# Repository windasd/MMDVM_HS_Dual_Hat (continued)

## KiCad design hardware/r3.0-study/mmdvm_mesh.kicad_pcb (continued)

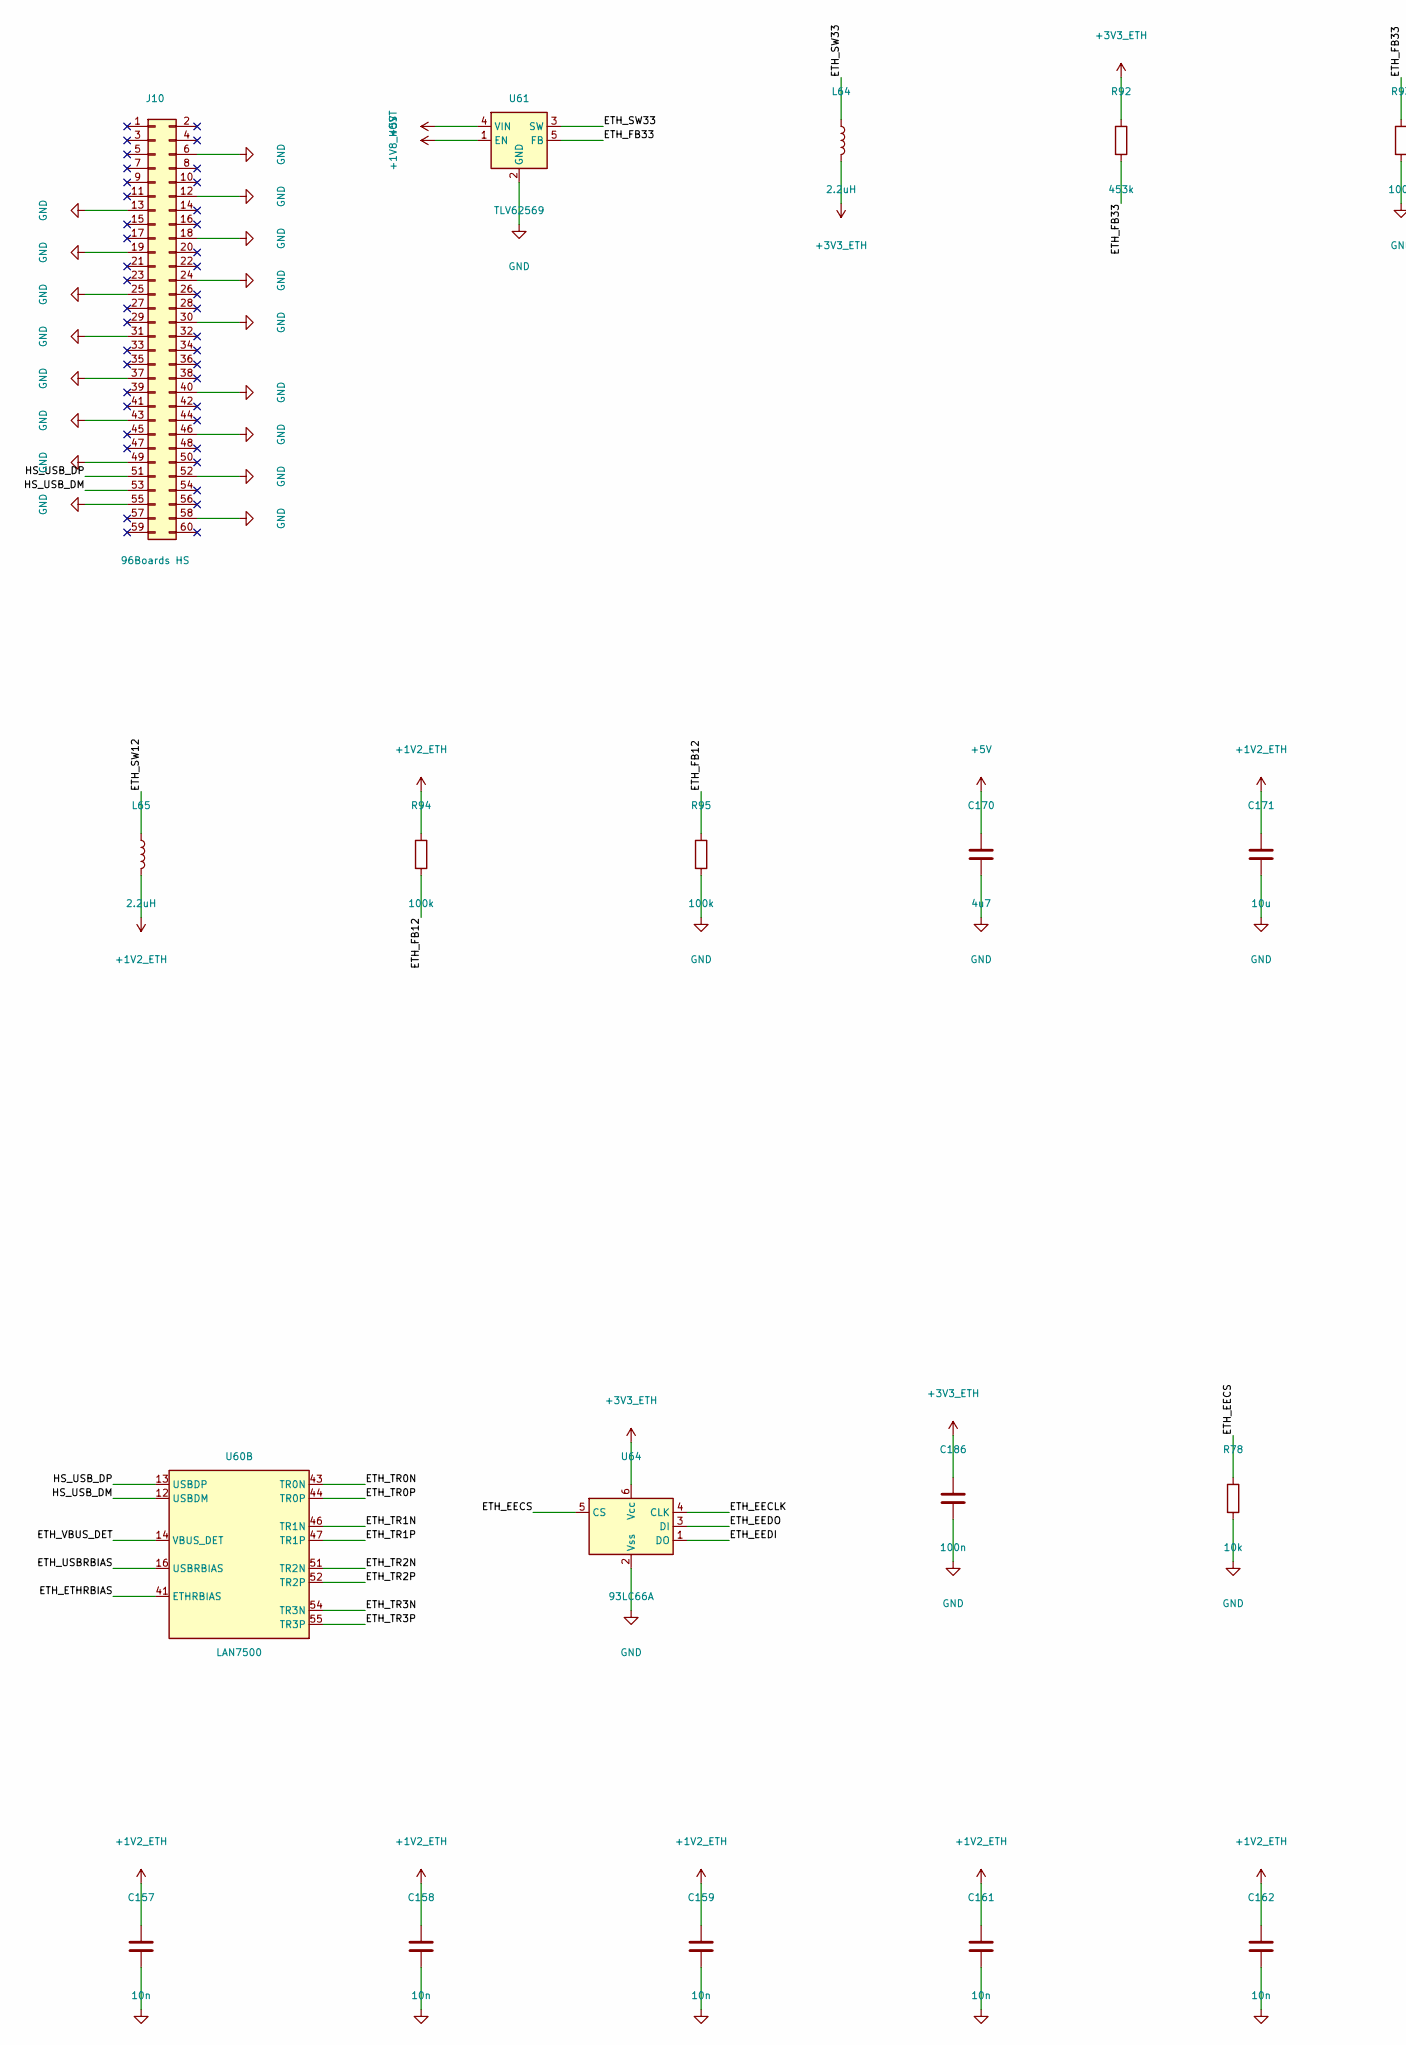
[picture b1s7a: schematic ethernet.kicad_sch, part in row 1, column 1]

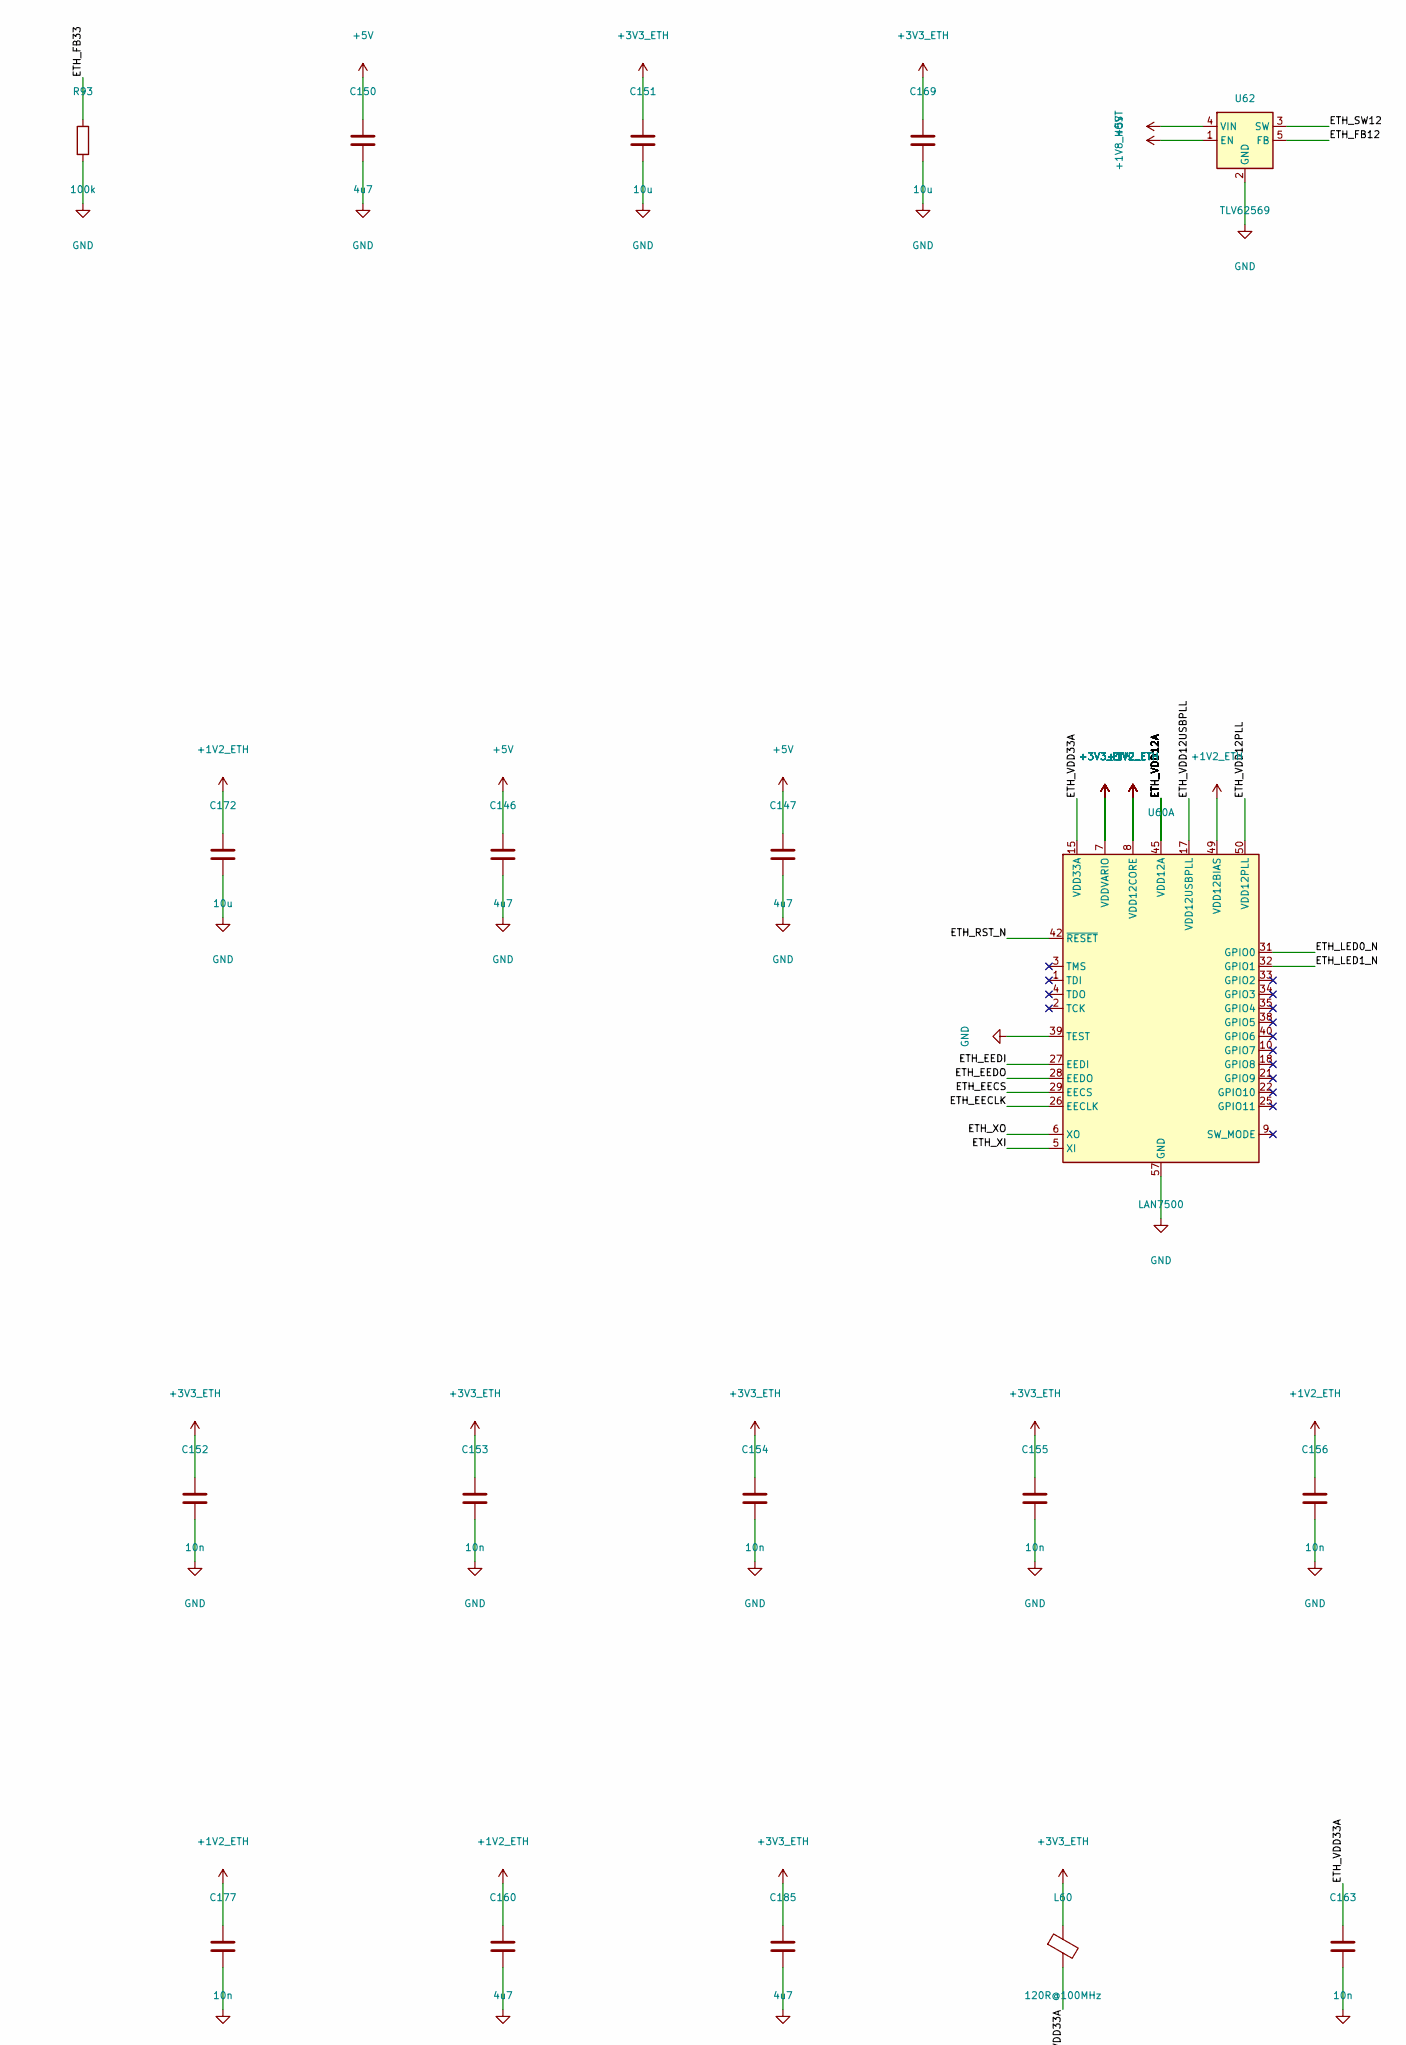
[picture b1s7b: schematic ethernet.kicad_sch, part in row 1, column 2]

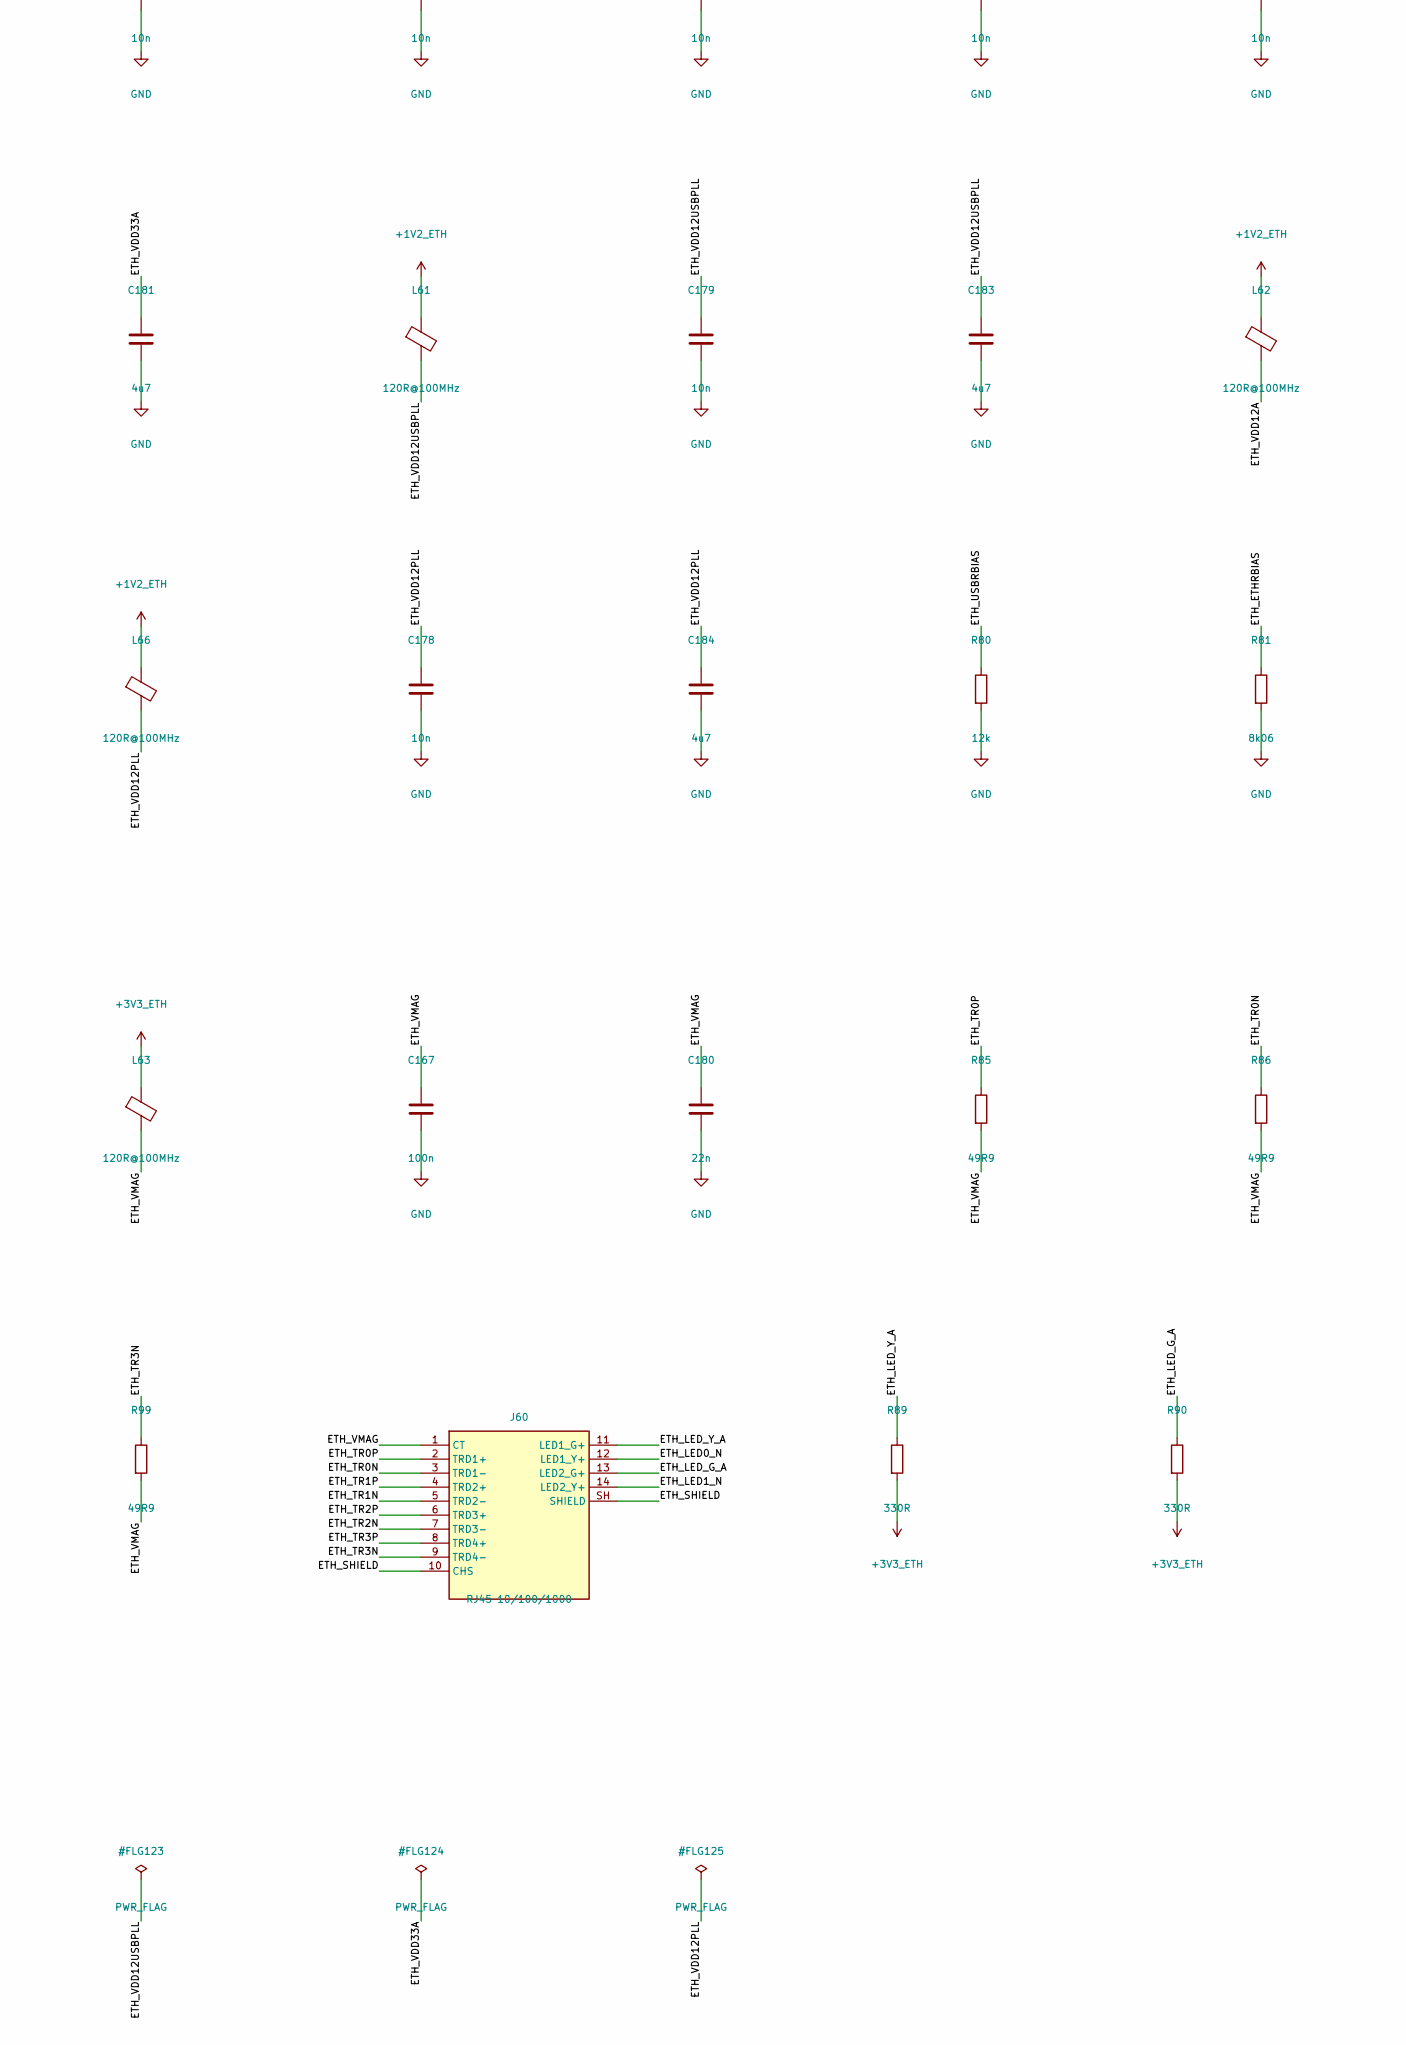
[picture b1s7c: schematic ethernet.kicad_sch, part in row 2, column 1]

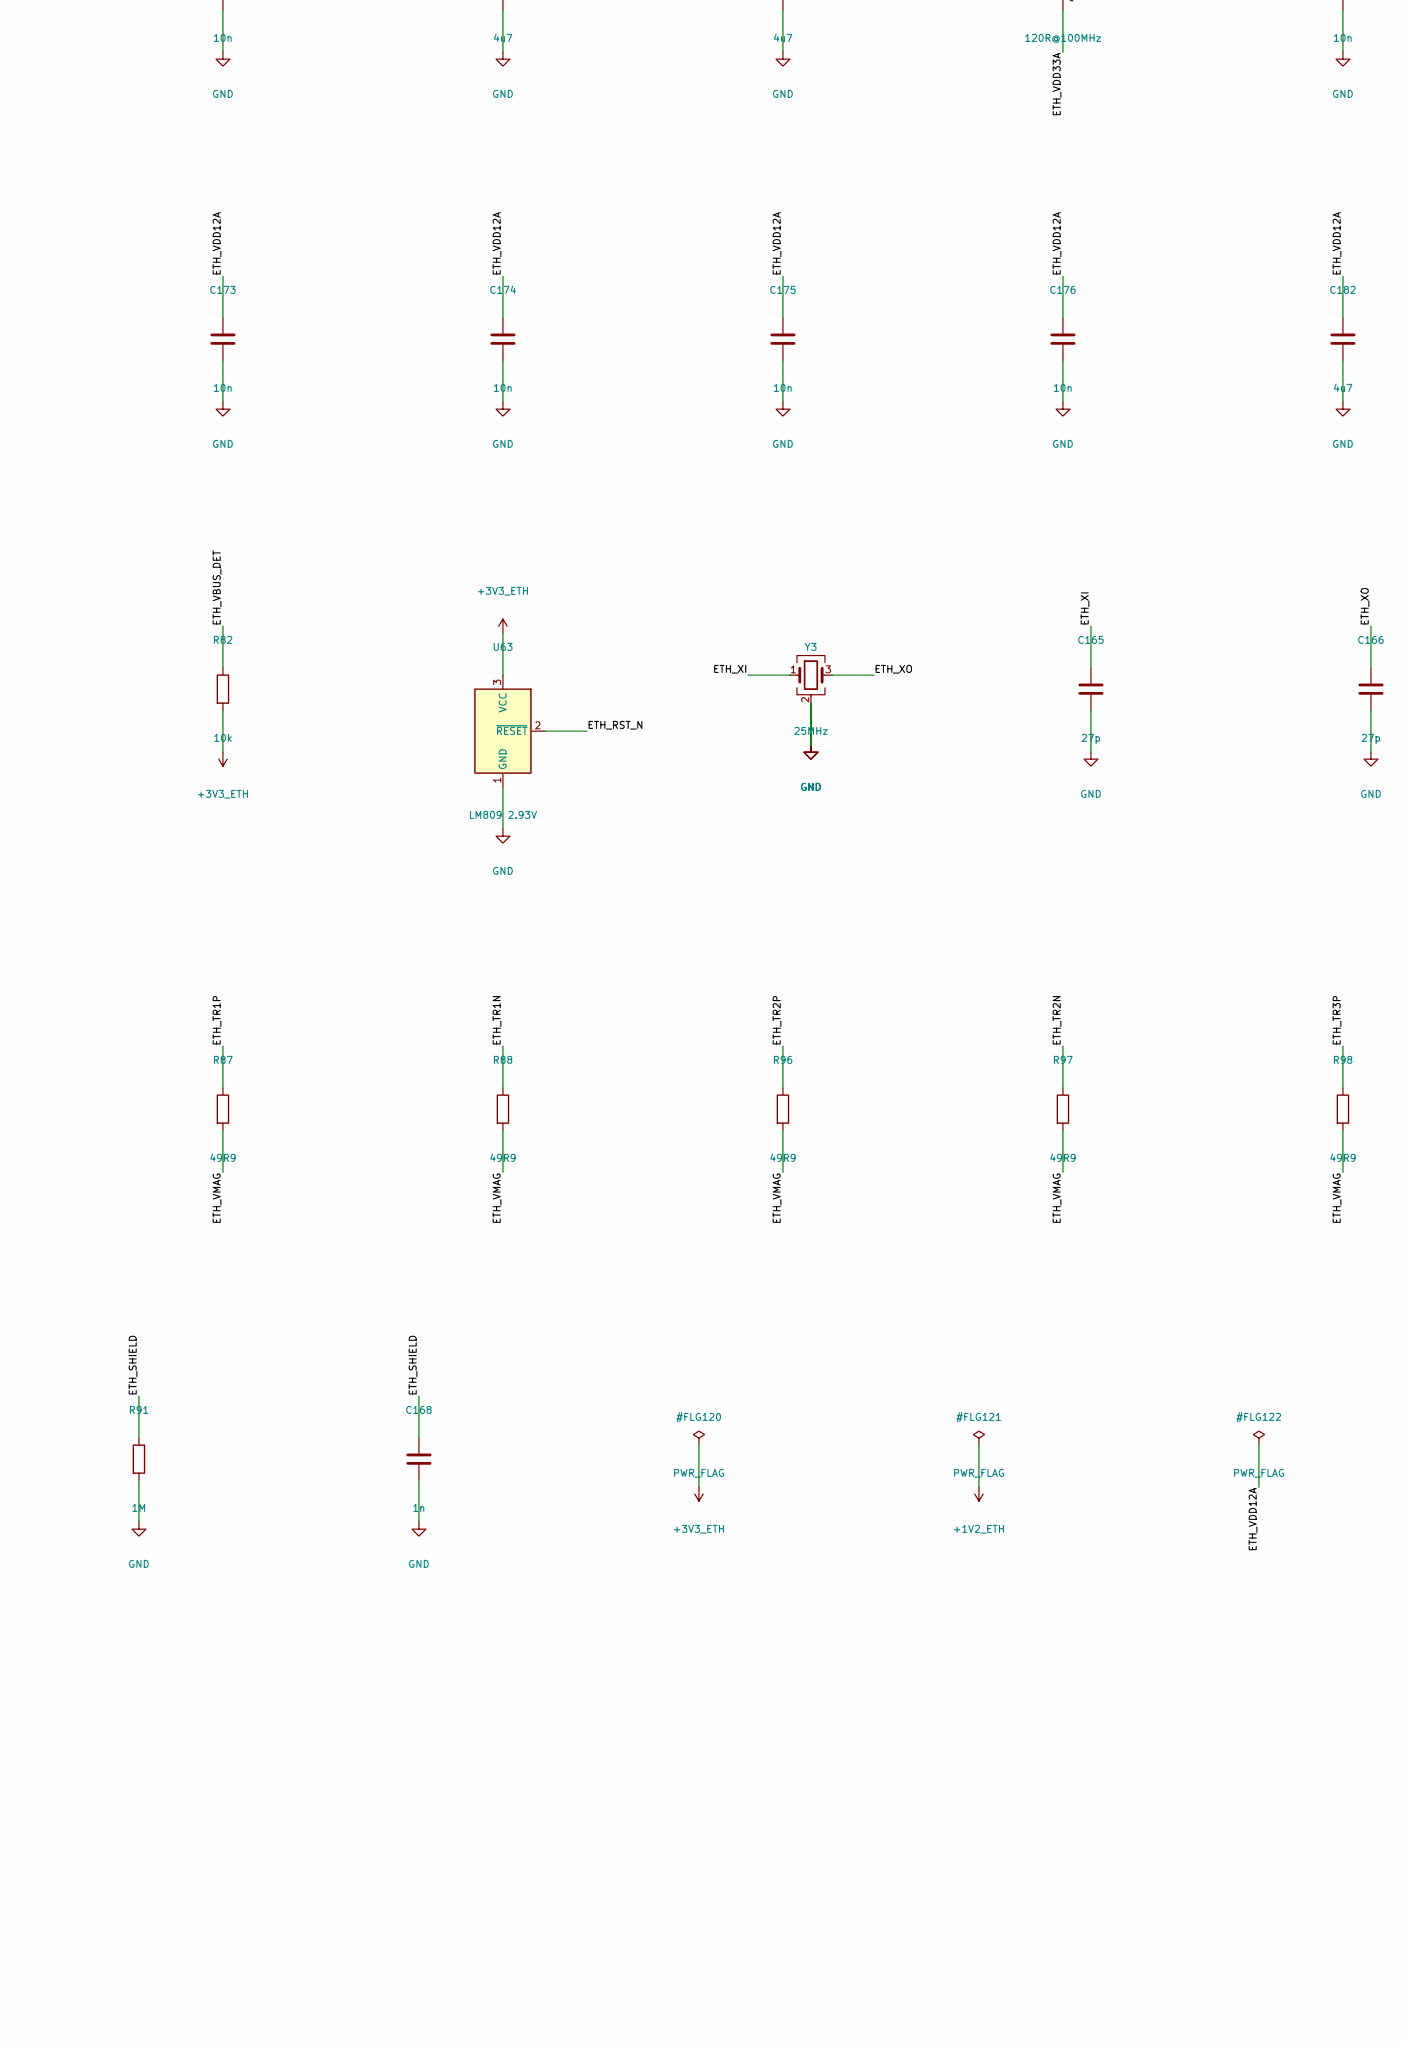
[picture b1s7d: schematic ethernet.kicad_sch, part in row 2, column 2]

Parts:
C146, C147: 4u7; C_0402_1005Metric; MPN CL05A475MP5NRNC; LCSC C23733
C150, C160, C170, C181, C182, C183, C184, C185: 4u7; C_0603_1608Metric; MPN CL10A475KO8NNNC; Mouser 187-CL10A475KO8NNNC
C151, C169, C171, C172: 10u; C_0603_1608Metric; MPN CL10A106MA8NRNC; Mouser 187-CL10A106MA8NRNC
C152, C153, C154, C155, C156, C157, C158, C159, C161, C162, C163, C173, C174, C175, C176, C177, C178, C179: 10n; C_0402_1005Metric; MPN CL05B103KB5NNNC; Mouser 187-CL05B103KB5NNNC
C165, C166: 27p; C_0402_1005Metric; MPN CL05C270JB5NNNC; LCSC C86287
C167, C186: 100n; C_0402_1005Metric; MPN CL05B104KO5NNNC; Mouser 187-CL05B104KO5NNNC
C168: 1n; C_1206_3216Metric; MPN CC1206KKX7RDBB102; LCSC C23631
C180: 22n; C_0402_1005Metric; MPN 0402B223K500NT; Mouser 187-CL05B223KB5NNNC (Mouser EQUIV: CL05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
J10: 96Boards HS; AMPHENOL_61083-063402LF; MPN 61083-063402LF; Mouser 649-61083-063402LF
J60: RJ45 10/100/1000; RJ45_Wuerth_7499111446_EdgeMount; MPN 7499111446; Mouser 710-7499111446
L60, L61, L62, L63, L66: 120R@100MHz; L_0603_1608Metric; MPN BLM18PG121SN1D; Mouser 81-BLM18PG121SN1D
L64, L65: 2.2uH; L_1008_2520Metric; MPN DFE252012F-2R2M=P2; Mouser 81-DFE252012F-2R2MP2
R78, R82: 10k; R_0402_1005Metric; MPN 0402WGF1002TCE; Mouser 603-RC0402FR-0710KL
R80: 12k; R_0402_1005Metric; MPN 0402WGF1202TCE; LCSC C25752
R81: 8k06; R_0402_1005Metric; MPN 0402WGF8061TCE; LCSC C25923
R85, R86, R87, R88, R96, R97, R98, R99: 49R9; R_0402_1005Metric; MPN 0402WGF499JTCE; LCSC C25120
R89, R90: 330R; R_0402_1005Metric; MPN 0402WGF3300TCE; Mouser 603-RC0402FR-07330RL
R91: 1M; R_1210_3225Metric; MPN 1210W2F1004T5E; Mouser 603-RC1210FR-071ML
R92: 453k; R_0402_1005Metric; MPN 0402WGF4533TCE; Mouser 603-RC0402FR-07453KL
R93, R94, R95: 100k; R_0402_1005Metric; MPN 0402WGF1003TCE; Mouser 603-RC0402FR-07100KL
U60: LAN7500; QFN-56-1EP_8x8mm_P0.5mm_EP5.9x5.9mm; MPN LAN7500I-ABZJ; Mouser 579-LAN7500-ABZJ
U61, U62: TLV62569; SOT-23-5; MPN TLV62569DBVR; Mouser 595-TLV62569DBVR
U63: LM809 2.93V; SOT-23; MPN LM809M3X-2.93/NOPB; Mouser 926-LM809M3X293NOPB
U64: 93LC66A; SOT-23-6; MPN 93LC66AT-I/OT; Mouser 579-93AA66AT-I/OT
Y3: 25MHz; Crystal_SMD_3225-4Pin_3.2x2.5mm; MPN X322525MRB4SI; Mouser 717-7M-25.000MAAJ-T

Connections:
+1V2_ETH: C156.1, C157.1, C158.1, C159.1, C160.1, C161.1, C162.1, C171.1, C172.1, C177.1, L61.1, L62.1, L65.2, L66.1, R94.1, U60.8 (VDD12CORE), U60.11 (VDD12CORE), U60.20 (VDD12CORE), U60.23 (VDD12CORE), U60.30 (VDD12CORE), U60.36 (VDD12CORE), U60.49 (VDD12BIAS)
+1V8_HOST: U61.1 (EN), U62.1 (EN); also elsewhere on the board
+3V3_ETH: C151.1, C152.1, C153.1, C154.1, C155.1, C169.1, C185.1, C186.1, L60.1, L63.1, L64.2, R82.2, R89.2, R90.2, R92.1, U60.7 (VDDVARIO), U60.19 (VDDVARIO), U60.24 (VDDVARIO), U60.37 (VDDVARIO), U63.3 (VCC), U64.6 (Vcc)
+5V: C146.1, C147.1, C150.1, C170.1, U61.4 (VIN), U62.4 (VIN); also elsewhere on the board
/Ethernet/ETH_EECLK: U60.26 (EECLK), U64.4 (CLK)
/Ethernet/ETH_EECS: R78.1, U60.29 (EECS), U64.5 (CS)
/Ethernet/ETH_EEDI: U60.27 (EEDI), U64.1 (DO)
/Ethernet/ETH_EEDO: U60.28 (EEDO), U64.3 (DI)
/Ethernet/ETH_ETHRBIAS: R81.1, U60.41 (ETHRBIAS)
/Ethernet/ETH_FB12: R94.2, R95.1, U62.5 (FB)
/Ethernet/ETH_FB33: R92.2, R93.1, U61.5 (FB)
/Ethernet/ETH_LED0_N: J60.12 (LED1_Y+), U60.31 (GPIO0)
/Ethernet/ETH_LED1_N: J60.14 (LED2_Y+), U60.32 (GPIO1)
/Ethernet/ETH_LED_G_A: J60.13 (LED2_G+), R90.1
/Ethernet/ETH_LED_Y_A: J60.11 (LED1_G+), R89.1
/Ethernet/ETH_RST_N: U60.42 (~RESET), U63.2 (~RESET)
/Ethernet/ETH_SHIELD: C168.1, J60.10 (CHS), J60.SH (SHIELD), R91.1
/Ethernet/ETH_SW12: L65.1, U62.3 (SW)
/Ethernet/ETH_SW33: L64.1, U61.3 (SW)
/Ethernet/ETH_TR0N: J60.3 (TRD1-), R86.1, U60.43 (TR0N)
/Ethernet/ETH_TR0P: J60.2 (TRD1+), R85.1, U60.44 (TR0P)
/Ethernet/ETH_TR1N: J60.5 (TRD2-), R88.1, U60.46 (TR1N)
/Ethernet/ETH_TR1P: J60.4 (TRD2+), R87.1, U60.47 (TR1P)
/Ethernet/ETH_TR2N: J60.7 (TRD3-), R97.1, U60.51 (TR2N)
/Ethernet/ETH_TR2P: J60.6 (TRD3+), R96.1, U60.52 (TR2P)
/Ethernet/ETH_TR3N: J60.9 (TRD4-), R99.1, U60.54 (TR3N)
/Ethernet/ETH_TR3P: J60.8 (TRD4+), R98.1, U60.55 (TR3P)
/Ethernet/ETH_USBRBIAS: R80.1, U60.16 (USBRBIAS)
/Ethernet/ETH_VBUS_DET: R82.1, U60.14 (VBUS_DET)
/Ethernet/ETH_VDD12A: C173.1, C174.1, C175.1, C176.1, C182.1, L62.2, U60.45 (VDD12A), U60.48 (VDD12A), U60.53 (VDD12A), U60.56 (VDD12A)
/Ethernet/ETH_VDD12PLL: C178.1, C184.1, L66.2, U60.50 (VDD12PLL)
/Ethernet/ETH_VDD12USBPLL: C179.1, C183.1, L61.2, U60.17 (VDD12USBPLL)
/Ethernet/ETH_VDD33A: C163.1, C181.1, L60.2, U60.15 (VDD33A)
/Ethernet/ETH_VMAG: C167.1, C180.1, J60.1 (CT), L63.2, R85.2, R86.2, R87.2, R88.2, R96.2, R97.2, R98.2, R99.2
/Ethernet/ETH_XI: C165.1, U60.5 (XI), Y3.1
/Ethernet/ETH_XO: C166.1, U60.6 (XO), Y3.3
/Ethernet/HS_USB_DM: J10.53, U60.12 (USBDM)
/Ethernet/HS_USB_DP: J10.51, U60.13 (USBDP)
GND: C146.2, C147.2, C150.2, C151.2, C152.2, C153.2, C154.2, C155.2, C156.2, C157.2, C158.2, C159.2, C160.2, C161.2, C162.2, C163.2, C165.2, C166.2, C167.2, C168.2, C169.2, C170.2, C171.2, C172.2, C173.2, C174.2, C175.2, C176.2, C177.2, C178.2, C179.2, C180.2, C181.2, C182.2, C183.2, C184.2, C185.2, C186.2, J10.6, J10.12, J10.13, J10.18, J10.19, J10.24, J10.25, J10.30, J10.31, J10.37, J10.40, J10.43, J10.46, J10.49, J10.52, J10.55, J10.58, R78.2, R80.2, R81.2, R91.2, R93.2, R95.2, U60.39 (TEST), U60.57 (GND), U61.2 (GND), U62.2 (GND), U63.1 (GND), U64.2 (Vss), Y3.2 (G), Y3.4 (G); also elsewhere on the board

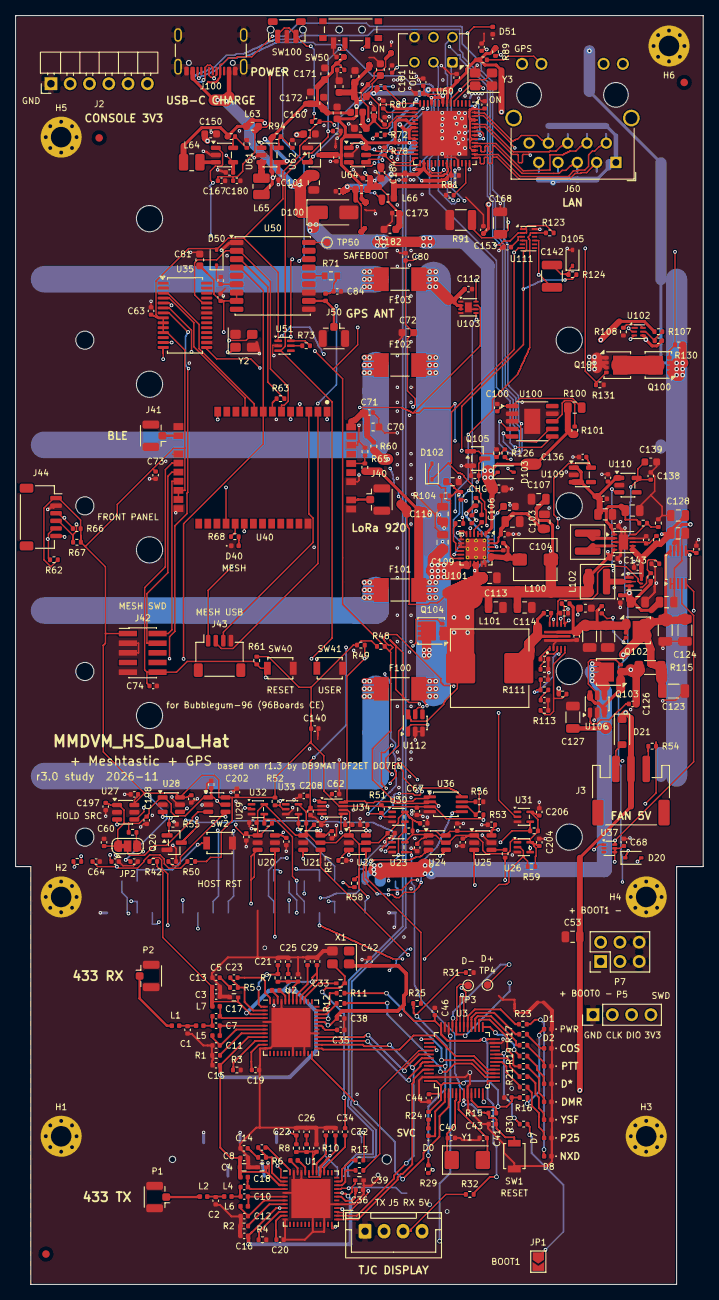
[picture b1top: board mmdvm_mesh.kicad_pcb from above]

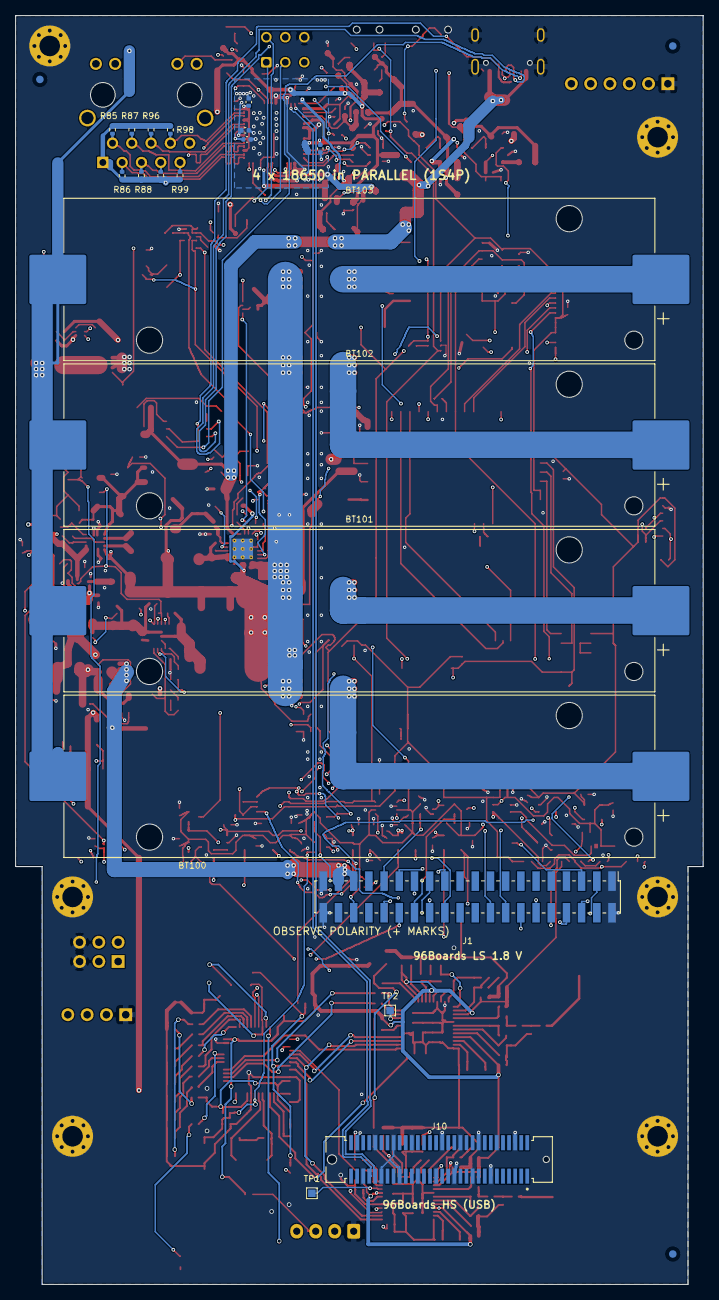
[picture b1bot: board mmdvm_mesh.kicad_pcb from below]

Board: 4 copper layers, 90.5 x 167.0 mm, 432 parts (23 on the bottom side), 263 nets.

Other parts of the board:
C187, C188, C189, C190, C191, C192, C193, C194, C195, C196, C197, C198, C199, C200, C201, C202, C203, C204, C205, C206, C207, C208: 100n; C_0402_1005Metric
FID1, FID2, FID3, FID4, FID5, FID6: Fiducial_1mm_Mask2mm
H1, H2, H3, H4, H5, H6: MountingHole_2.7mm_M2.5_Pad_Via

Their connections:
+1V8_HOST: C187.1, C189.1, C191.1, C193.1, C195.1, C197.1, C199.1, C201.1, C203.1, C204.1, C205.1, C206.1, C207.1, C208.1; also elsewhere on the board
+3V3: C188.1, C190.1, C192.1, C194.1, C196.1; also elsewhere on the board
+3V3_MESH: C198.1, C200.1, C202.1; also elsewhere on the board
GND: C187.2, C188.2, C189.2, C190.2, C191.2, C192.2, C193.2, C194.2, C195.2, C196.2, C197.2, C198.2, C199.2, C200.2, C201.2, C202.2, C203.2, C204.2, C205.2, C206.2, C207.2, C208.2, H1.1, H2.1, H3.1, H4.1, H5.1, H6.1; also elsewhere on the board

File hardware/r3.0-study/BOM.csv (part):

"Reference","Value","Footprint","Qty","MFR","MPN","Mouser","Mouser MPN (if different)","LCSC"
"BT100,BT101,BT102,BT103","18650","Battery:BatteryHolder_Keystone_1042_1x18650","4","Keystone Electronics","1042P","534-1042P","","C6038009"
"C1,C2,C11,C12","6p8","Capacitor_SMD:C_0402_1005Metric","4","Murata Electronics","GJM1555C1H6R8BB01D","81-GJM1555C1H6R8BB1D","","C88896"
"C3,C15,C16,C31,C32,C38,C42","10n","Capacitor_SMD:C_0402_1005Metric","7","Vishay / Vitramon","VJ0402Y103KXJCW1BC","77-VJ0402Y103KXJCBC","","C15195"
"C4,C17,C18,C39","10n","MMDVM:C_0402","4","Vishay / Vitramon","VJ0402Y103KXJCW1BC","77-VJ0402Y103KXJCBC","","C15195"
"C5,C8","220p","Capacitor_SMD:C_0402_1005Metric","2","Murata Electronics","GRM1555C1H221JA01D","81-GRM1555C1H221JA01","","C71693"
"C6,C9","10p","Capacitor_SMD:C_0402_1005Metric","2","Murata Electronics","GRM1555C1E100GA01D","81-GRM1555C1E100GA1D","","C76945"
"C7,C10","4p7","Capacitor_SMD:C_0402_1005Metric","2","Murata Electronics","GRM1555C1H4R7CA01D","81-GRM1555C1H4R7CA1D","","C85883"
"C13,C14,C19,C20,C29,C30,C35,C36","100n","Capacitor_SMD:C_0402_1005Metric","8","Murata Electronics","GCM155R71C104KA55D","81-GCM155R71C104KA5J","GCM155R71C104KA55J","C1525"
"C21,C22","470p","Capacitor_SMD:C_0402_1005Metric","2","Murata Electronics","GCM1555C1H471JA16J","81-GCM1555C1H471JA6J","","C76971"
"C23,C24","22n","Capacitor_SMD:C_0402_1005Metric","2","Murata Electronics","GCM155R71E223KA55D","81-GCM155R71E223KA5D","","C126528"
"C25,C26","15n","Capacitor_SMD:C_0402_1005Metric","2","Murata Electronics","GRM155R71C153KA01J","81-GRM155R71C153KA1J","","C113050"
"C27,C28","1n","Capacitor_SMD:C_0402_1005Metric","2","Murata Electronics","GRM155R60J102KA01D","81-GRM155R60J102KA1D","","C710871"
"C33","22p","MMDVM:C_0402","1","Kyocera AVX","KGM05ACG1H220GH","581-KGM05ACG1H220GH","","C161541"
"C34","22p","Capacitor_SMD:C_0402_1005Metric","1","Kyocera AVX","KGM05ACG1H220GH","581-KGM05ACG1H220GH","","C161541"
"C40,C41","20p","Capacitor_SMD:C_0402_1005Metric","2","Murata Electronics","GJM1555C1H200FB01D","81-GJM1555C1H200FB1D","","C913479"
"C43,C44,C45,C46,C61,C62,C63,C64,C67,C68,C71,C73,C74,C82,C111,C112,C115,C125,C126,C131,C140,C167,C186","100n","Capacitor_SMD:C_0402_1005Metric","23","Samsung Electro-Mechanics","CL05B104KO5NNNC","187-CL05B104KO5NNNC","","C1525"
"C53,C101,C103,C104,C109,C110,C128,C132,C133,C134","10u","Capacitor_SMD:C_0805_2012Metric","10","Samsung Electro-Mechanics","CL21A106KAYNNNE","187-CL21A106KAYNNNE","","C15850"
"C60,C80,C83,C100,C135,C136,C137,C138,C141,C145,C148","1u","Capacitor_SMD:C_0402_1005Metric","11","Samsung Electro-Mechanics","CL05A105KA5NQNC","187-CL05A105KA5NQNC","","C52923"
"C65,C66","22p","Capacitor_SMD:C_0402_1005Metric","2","FH (Guangdong Fenghua Advanced Tech)","0402CG220J500NT","187-CL05C220JB5NNNC (Mouser EQUIV: CL05C220JB5NNNC)","","C1555"
"C70,C72,C81,C139,C151,C169,C171,C172","10u","Capacitor_SMD:C_0603_1608Metric","8","Samsung Electro-Mechanics","CL10A106MA8NRNC","187-CL10A106MA8NRNC","","C96446"
"C84,C152,C153,C154,C155,C156,C157,C158,C159,C161,C162,C163,C173,C174,C175,C176,C177,C178,C179","10n","Capacitor_SMD:C_0402_1005Metric","19","Samsung Electro-Mechanics","CL05B103KB5NNNC","187-CL05B103KB5NNNC","","C15195"
"C102","1u","Capacitor_SMD:C_0603_1608Metric","1","Samsung Electro-Mechanics","CL10A105KB8NNNC","187-CL10A105KB8NNNC","","C15849"
"C105","47n","Capacitor_SMD:C_0402_1005Metric","1","Samsung Electro-Mechanics","CL05B473KO5NNNC","187-CL05B473KO5NNNC","","C307434"
"C106,C116,C150,C160,C170,C181,C182,C183,C184,C185","4u7","Capacitor_SMD:C_0603_1608Metric","10","Samsung Electro-Mechanics","CL10A475KO8NNNC","187-CL10A475KO8NNNC","","C19666"
"C107,C108,C113,C114,C129,C130","22u","Capacitor_SMD:C_0805_2012Metric","6","Samsung Electro-Mechanics","CL21A226MAQNNNE","187-CL21A226MOQNNNE (Mouser EQUIV: CL21A226MOQNNNE)","","C45783"
"C117","6n8","Capacitor_SMD:C_0402_1005Metric","1","Samsung Electro-Mechanics","CL05B682KB5NNNC","187-CL05B682KB5NNNC","","C318580"
"C118","10p","Capacitor_SMD:C_0402_1005Metric","1","Samsung Electro-Mechanics","CL05C100JB5NNNC","187-CL05C100JB5NNNC","","C32949"
"C119,C120,C127","10u","Capacitor_SMD:C_1206_3216Metric","3","Samsung Electro-Mechanics","CL31A106KBHNNNE","187-CL31A106KBHNNNE","","C13585"
"C121,C180","22n","Capacitor_SMD:C_0402_1005Metric","2","FH (Guangdong Fenghua Advanced Tech)","0402B223K500NT","187-CL05B223KB5NNNC (Mouser EQUIV: CL05B223KB5NNNC)","","C1532"
"C122,C123,C124","22u","Capacitor_SMD:C_1206_3216Metric","3","Samsung Electro-Mechanics","CL31A226KAHNNNE","187-CL31A226KAHNNNE","","C12891"
"C143,C144","10u","Capacitor_SMD:C_0402_1005Metric","2","Samsung Electro-Mechanics","CL05A106MQ5NUNC","","","C15525"
"C146,C147,C149","4u7","Capacitor_SMD:C_0402_1005Metric","3","Samsung Electro-Mechanics","CL05A475MP5NRNC","","","C23733"
"C165,C166","27p","Capacitor_SMD:C_0402_1005Metric","2","Samsung Electro-Mechanics","CL05C270JB5NNNC","","","C86287"
"C168","1n","Capacitor_SMD:C_1206_3216Metric","1","Yageo","CC1206KKX7RDBB102","","","C23631"
"D0,D3,D7","red","LED_SMD:LED_0402_1005Metric","3","Kingbright","APHHS1005SURCK","604-APHHS1005SURCK","","C2852592"
"D1,D4,D40,D51","green","LED_SMD:LED_0402_1005Metric","4","Kingbright","APHHS1005LCGCK","604-APHHS1005CGCK","APHHS1005CGCK","C5354975"
"D2,D5","yellow","LED_SMD:LED_0402_1005Metric","2","Kingbright","APHHS1005SYCK","604-APHHS1005SYCK","","C5875733"
"D6","amber","LED_SMD:LED_0402_1005Metric","1","Kingbright","APHHS1005SECK","604-APHHS1005SECK","","C5875753"
"D8","blue","LED_SMD:LED_0402_1005Metric","1","Kingbright","APHHS1005QBC/D","604-APHHS1005QBCD","","C2853064"
"D21","B5819W","Diode_SMD:D_SOD-123","1","MCC (Micro Commercial Components)","B5819W-TP","833-B5819W-TP","","C84354"
"D50,D102","BAT54","Diode_SMD:D_SOD-323","2","onsemi","BAT54HT1G","863-BAT54HT1G","","C21107"
"D100","SMAJ15CA","Diode_SMD:D_SMA","1","Littelfuse","SMAJ15CA","576-SMAJ15CA","","C223985"
"D101","orange","LED_SMD:LED_0402_1005Metric","1","Kingbright","APHHS1005SECK","604-APHHS1005SECK","","C5875753"
"D103","6V2","Diode_SMD:D_SOD-323","1","onsemi","MM3Z6V2T1G","","","C393369"
"F100,F101,F102,F103","7A","Fuse:Fuse_Littelfuse-NANO2-451_453","4","Littelfuse","0451007.MRL","576-0451007.MRL","","C99548"
"J1","96Boards LS","MMDVM_r30:LS_2x20_P2.00mm_SMD_MezzanineBottom","1","Amphenol FCI","57202-G52-20LF","649-57202-G52-20LF","","C5422271"
"J2","CONSOLE 3V3","MMDVM_r30:PinHeader_1x06_P2.54mm_Horizontal_EdgeMount","1","Wurth Elektronik","61300611021","710-61300611021","","C6461553"
"J3","FAN 30x30x10 5V","Connector_JST:JST_PH_S3B-PH-SM4-TB_1x03-1MP_P2.00mm_Horizontal","1","JST","S3B-PH-SM4-TB(LF)(SN)","306-S3BPHSM4TBLFSN","","C265101"
"J5","TJC display","Connector_JST:JST_XH_B4B-XH-A_1x04_P2.50mm_Vertical","1","JST","B4B-XH-A(LF)(SN)","306-B4BXHALFSN","","C144395"
"J10","96Boards HS","MMDVM_r30:AMPHENOL_61083-063402LF","1","Amphenol ICC (FCI)","61083-063402LF","649-61083-063402LF","","C254700"
"J40","LoRa 920 U.FL","Connector_Coaxial:U.FL_Hirose_U.FL-R-SMT-1_Vertical","1","Hirose","U.FL-R-SMT-1(10)","798-U.FL-R-SMT-110","","C88373"
"J41","BLE U.FL","Connector_Coaxial:U.FL_Hirose_U.FL-R-SMT-1_Vertical","1","Hirose","U.FL-R-SMT-1(10)","798-U.FL-R-SMT-110","","C88373"
"J42","MESH SWD","Connector_PinHeader_1.27mm:PinHeader_2x05_P1.27mm_Vertical_SMD","1","Samtec","FTSH-105-01-F-DV-K","200-FTSH10501FDVK","","C5382952"
"J43","MESH USB","Connector_JST:JST_SH_SM04B-SRSS-TB_1x04-1MP_P1.00mm_Horizontal","1","JST","SM04B-SRSS-TB(LF)(SN)","306-SM04BSRSSTBLFSN","","C160404"
"J44","FRONT PANEL","Connector_JST:JST_SH_SM06B-SRSS-TB_1x06-1MP_P1.00mm_Horizontal","1","JST","SM06B-SRSS-TB(LF)(SN)","306-M06BSRSSTBLFSNPP","","C160405"
"J50","GPS U.FL","Connector_Coaxial:U.FL_Hirose_U.FL-R-SMT-1_Vertical","1","Hirose","U.FL-R-SMT-1(10)","798-U.FL-R-SMT-110","","C88373"
"J60","RJ45 10/100/1000","MMDVM_r30:RJ45_Wuerth_7499111446_EdgeMount","1","Wurth Elektronik","7499111446","710-7499111446","","C5542783"
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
